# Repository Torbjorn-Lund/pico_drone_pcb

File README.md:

# pico_drone_pcb

Custom PCB for a Raspberry Pi Pico–powered drone.  

This board integrates the core electronics needed to run a quadcopter, with power regulation, sensor connectors, and interfaces for ESCs and other peripherals.

The corresponding code, written in c can be found [here](https://github.com/Torbjorn-Lund/pico_drone_project)

## Features
- Designed for **Raspberry Pi Pico 2**  
- Power regulation:
  - Buck converter supporting up to **18 V input**
  - **TVS diode protection** limiting input voltage to ~10 V  
  - Optimized for **2S LiPo batteries (≈7.4 V nominal, 8.4 V fully charged)**  
- Breakouts for:
  - ESCs (dshot)
  - IMU (ICM-20948)  
  - Barometer (BMP280)  
  - GPS (NEO-M8N)  
  - Time-of-flight sensor (VL53L1X)  

## Images

## Notes / Limitations
- TVS diode limits voltage, so this board is not suitable for 3S+ LiPo packs.  
- Board is still under development.

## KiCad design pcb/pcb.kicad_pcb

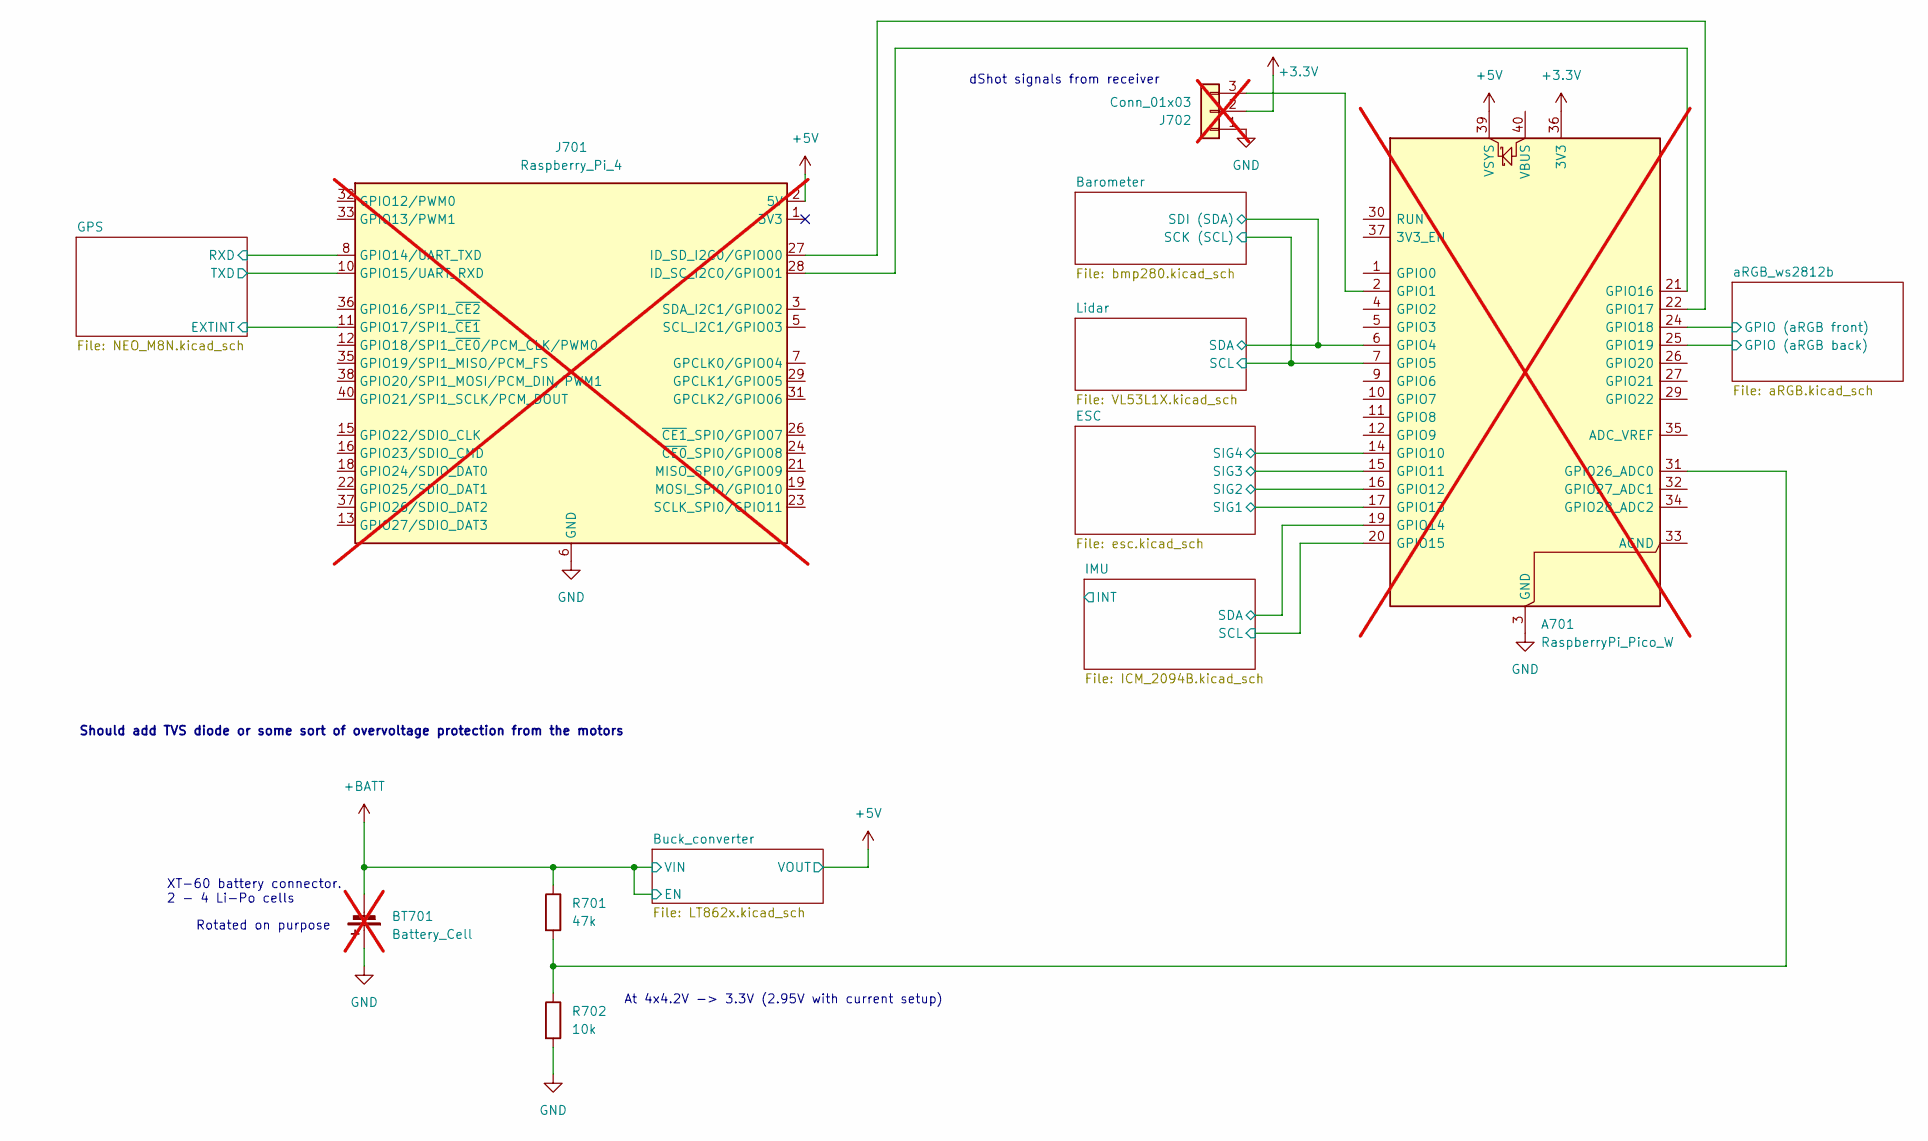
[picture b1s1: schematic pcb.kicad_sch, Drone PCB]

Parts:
A701: RaspberryPi_Pico_W; RaspberryPi_Pico_SMD_HandSolder; DigiKey 0; not fitted
BT701: Battery_Cell; AMASS_XT60-M_1x02_P7.20mm_Vertical; DigiKey 1738-1437-ND; not fitted
J701: Raspberry_Pi_4; PinSocket_2x20_P2.54mm_Vertical; not fitted
J702: Conn_01x03; PinHeader_1x03_P2.54mm_Horizontal; not fitted
R701: 47k; R_0402_1005Metric_Pad0.72x0.64mm_HandSolder
R702: 10k; R_0402_1005Metric_Pad0.72x0.64mm_HandSolder

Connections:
+3.3V: A701.36 (3V3), J702.2; also elsewhere on the board
+5V: A701.39 (VSYS), J701.2 (5V), J701.4 (5V); also elsewhere on the board
+BATT: BT701.2 (-), R701.1; also elsewhere on the board
/Barometer/SCK (SCL): A701.7 (GPIO5); also elsewhere on the board
/Barometer/SDI (SDA): A701.6 (GPIO4); also elsewhere on the board
/ESC/SIG1: A701.17 (GPIO13); also elsewhere on the board
/ESC/SIG2: A701.16 (GPIO12); also elsewhere on the board
/ESC/SIG3: A701.15 (GPIO11); also elsewhere on the board
/ESC/SIG4: A701.14 (GPIO10); also elsewhere on the board
/GPS/EXTINT: J701.11 (GPIO17/SPI1_~CE1); also elsewhere on the board
/GPS/RXD: J701.8 (GPIO14/UART_TXD); also elsewhere on the board
/GPS/TXD: J701.10 (GPIO15/UART_RXD); also elsewhere on the board
/IMU/SCL: A701.20 (GPIO15); also elsewhere on the board
/IMU/SDA: A701.19 (GPIO14); also elsewhere on the board
/aRGB_ws2812b/GPIO (aRGB back): A701.25 (GPIO19); also elsewhere on the board
/aRGB_ws2812b/GPIO (aRGB front): A701.24 (GPIO18); also elsewhere on the board
GND: A701.3 (GND), A701.8 (GND), A701.13 (GND), A701.18 (GND), A701.23 (GND), A701.28 (GND), A701.38 (GND), BT701.1 (+), J701.6 (GND), J701.9 (GND), J701.14 (GND), J701.20 (GND), J701.25 (GND), J701.30 (GND), J701.34 (GND), J701.39 (GND), J702.1, R702.2; also elsewhere on the board
unnamed: A701.2 (GPIO1), J702.3
unnamed: A701.21 (GPIO16), J701.28 (ID_SC_I2C0/GPIO01)
unnamed: A701.22 (GPIO17), J701.27 (ID_SD_I2C0/GPIO00)
unnamed: A701.31 (GPIO26_ADC0), R701.2, R702.1

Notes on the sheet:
At 4x4.2V -> 3.3V (2.95V with current setup)
Rotated on purpose
dShot signals from receiver
XT-60 battery connector. 2 - 4 Li-Po cells
Should add TVS diode or some sort of overvoltage protection from the motors

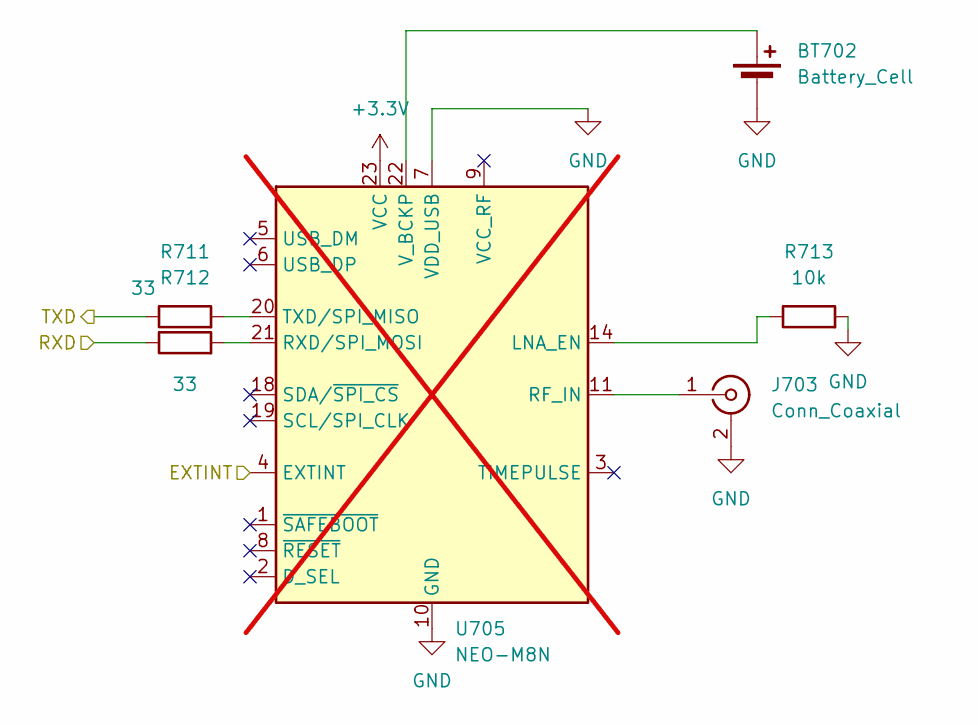
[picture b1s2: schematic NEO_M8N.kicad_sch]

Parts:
BT702: Battery_Cell; BatteryHolder_Keystone_3034_1x20mm; DigiKey 36-3034-ND
J703: Conn_Coaxial; U.FL_Hirose_U.FL-R-SMT-1_Vertical; DigiKey 26-U.FL-R-SMT-1(60)CT-ND
R711, R712: 33; R_0402_1005Metric_Pad0.72x0.64mm_HandSolder
R713: 10k; R_0402_1005Metric_Pad0.72x0.64mm_HandSolder
U705: NEO-M8N; ublox_NEO; DigiKey 672-NEO-M8N-0CT-ND; not fitted

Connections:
+3.3V: U705.23 (VCC); also elsewhere on the board
/GPS/EXTINT: U705.4 (EXTINT); also elsewhere on the board
/GPS/RXD: R712.1; also elsewhere on the board
/GPS/TXD: R711.1; also elsewhere on the board
GND: BT702.2 (-), J703.2 (Ext), R713.2, U705.7 (VDD_USB), U705.10 (GND), U705.12 (GND), U705.13 (GND), U705.24 (GND); also elsewhere on the board
unnamed: BT702.1 (+), U705.22 (V_BCKP)
unnamed: J703.1 (In), U705.11 (RF_IN)
unnamed: R713.1, U705.14 (LNA_EN)
unnamed: R712.2, U705.21 (RXD/SPI_MOSI)
unnamed: R711.2, U705.20 (TXD/SPI_MISO)

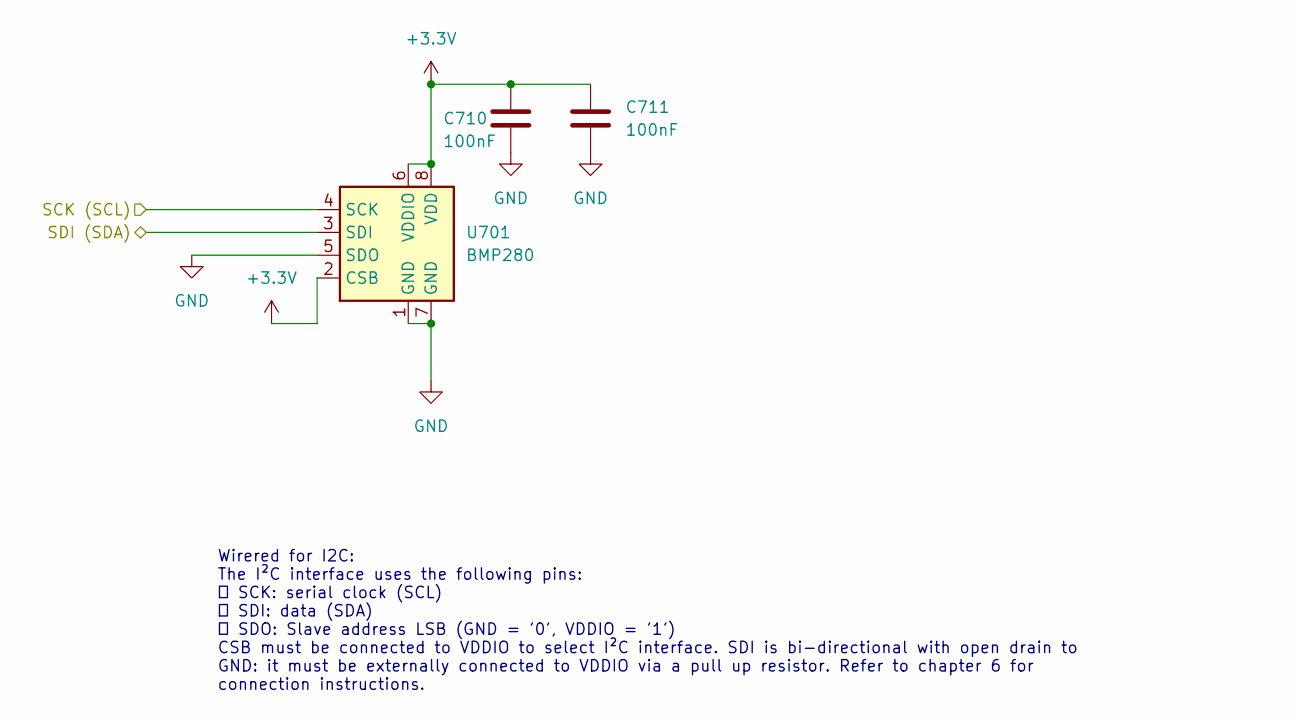
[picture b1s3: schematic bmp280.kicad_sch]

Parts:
C710, C711: 100nF; C_0402_1005Metric_Pad0.74x0.62mm_HandSolder
U701: BMP280; Bosch_LGA-8_2x2.5mm_P0.65mm_ClockwisePinNumbering; DigiKey 828-1064-2-ND

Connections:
+3.3V: C710.1, C711.1, U701.2 (CSB), U701.6 (VDDIO), U701.8 (VDD); also elsewhere on the board
/Barometer/SCK (SCL): U701.4 (SCK); also elsewhere on the board
/Barometer/SDI (SDA): U701.3 (SDI); also elsewhere on the board
GND: C710.2, C711.2, U701.1 (GND), U701.5 (SDO), U701.7 (GND); also elsewhere on the board

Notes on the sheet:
Wirered for I2C: The I²C interface uses the following pins:  SCK: serial clock (SCL)  SDI: data (SDA)  SDO: Slave address LSB (GND = '0', VDDIO = '1') CSB must be connected to VDDIO to select I²C interface. SDI is bi-directional with open drain to GND: it must be externally connected to VDDIO vi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

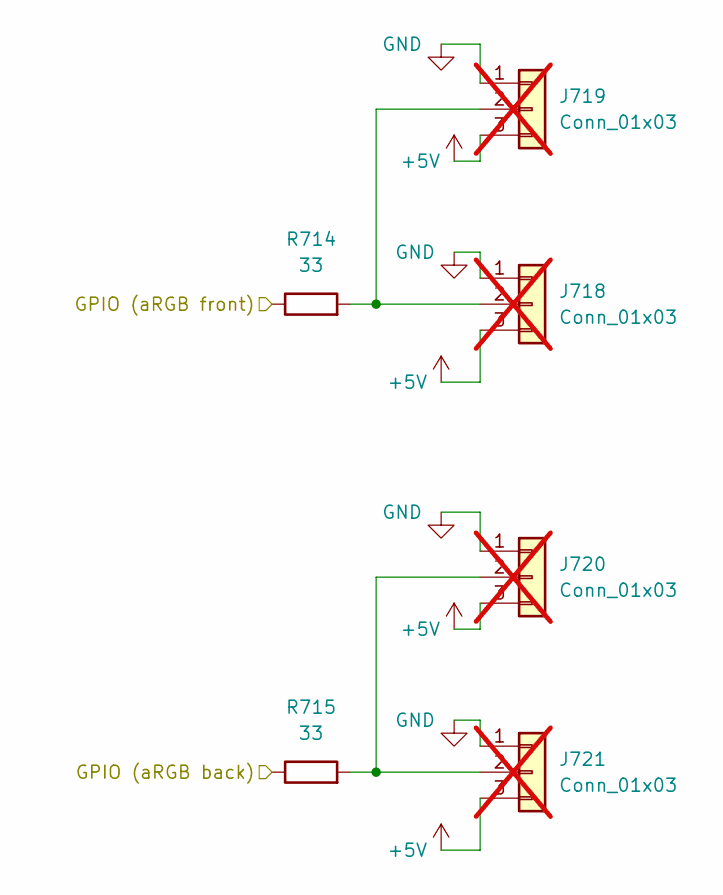
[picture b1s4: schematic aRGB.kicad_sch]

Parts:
J718, J719, J720, J721: Conn_01x03; aRGB_LED_PAD_CONN; not fitted
R714, R715: 33; R_0402_1005Metric_Pad0.72x0.64mm_HandSolder

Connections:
+5V: J718.3, J719.3, J720.3, J721.3; also elsewhere on the board
/aRGB_ws2812b/GPIO (aRGB back): R715.1; also elsewhere on the board
/aRGB_ws2812b/GPIO (aRGB front): R714.1; also elsewhere on the board
GND: J718.1, J719.1, J720.1, J721.1; also elsewhere on the board
unnamed: J718.2, J719.2, R714.2
unnamed: J720.2, J721.2, R715.2

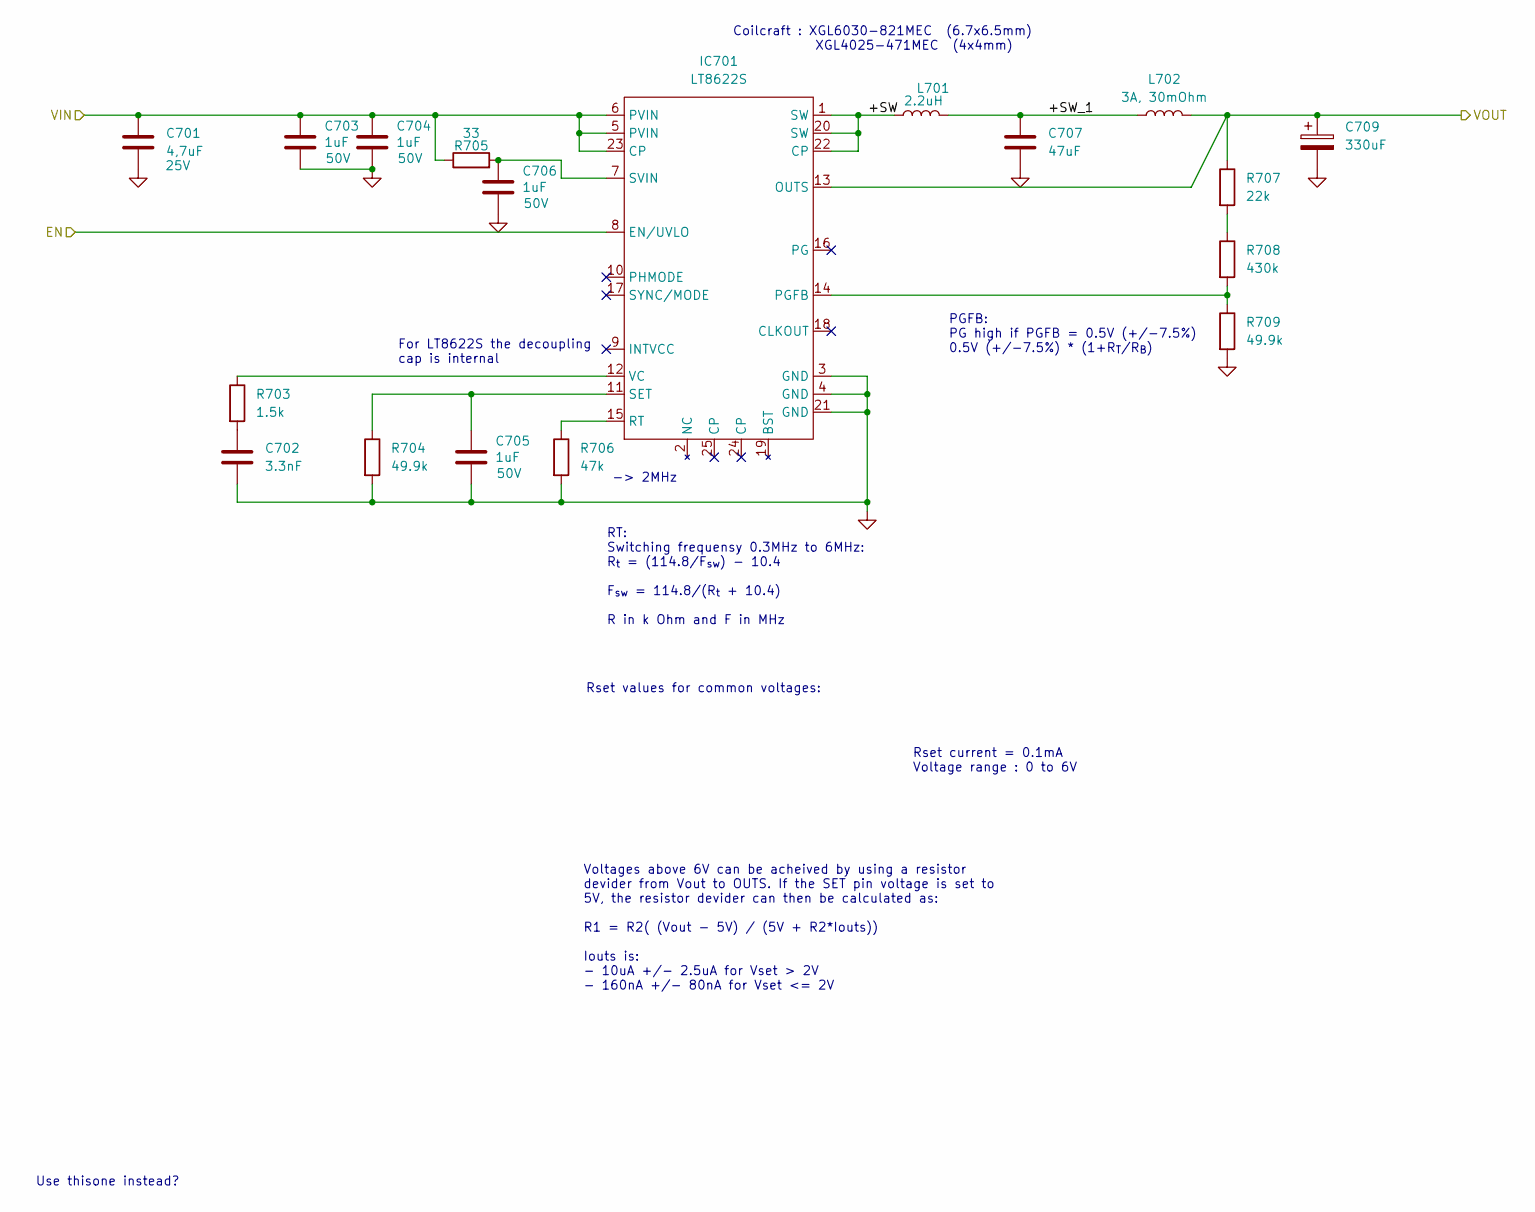
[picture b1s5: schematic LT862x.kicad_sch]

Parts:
C701: 4,7uF; C_0402_1005Metric_Pad0.74x0.62mm_HandSolder; Voltage 25V; DigiKey 490-GRM155C61E475ME15DCT-ND
C702: 3.3nF; C_0402_1005Metric_Pad0.74x0.62mm_HandSolder
C703, C704, C705, C706: 1uF; C_0402_1005Metric_Pad0.74x0.62mm_HandSolder; Voltage 50V; DigiKey 490-GRM155R61H105KE05DCT-ND
C707: 47uF; C_1206_3216Metric_Pad1.33x1.80mm_HandSolder; DigiKey 445-8047-1-ND
C709: 330uF; CAPMP7343X430N
IC701: LT8622S; QFN-20; DigiKey 505-LT8622SAV#PBF-ND
L701: 2.2uH; L_Coilcraft_XAL6060-XXX; DigiKey 4044-CSEG0660-2R2MCT-ND
L702: 3A, 30mOhm; L_0603_1608Metric_Pad1.05x0.95mm_HandSolder; DigiKey 490-5254-1-ND
R703: 1.5k; R_0402_1005Metric_Pad0.72x0.64mm_HandSolder
R704, R709: 49.9k; R_0402_1005Metric_Pad0.72x0.64mm_HandSolder
R705: 33; R_0402_1005Metric_Pad0.72x0.64mm_HandSolder
R706: 47k; R_0402_1005Metric_Pad0.72x0.64mm_HandSolder
R707: 22k; R_0402_1005Metric_Pad0.72x0.64mm_HandSolder
R708: 430k; R_0402_1005Metric_Pad0.72x0.64mm_HandSolder

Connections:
+5V: C709.1, IC701.13 (OUTS), L702.2, R707.1; also elsewhere on the board
+BATT: C701.1, C703.1, C704.1, IC701.5 (PVIN), IC701.6 (PVIN), IC701.8 (EN/UVLO), IC701.23 (CP), R705.1; also elsewhere on the board
/Buck_converter/+SW: IC701.1 (SW), IC701.20 (SW), IC701.22 (CP), L701.1
/Buck_converter/+SW_1: C707.1, L701.2, L702.1
GND: C701.2, C702.2, C703.2, C704.2, C705.2, C706.2, C707.2, C709.2, IC701.3 (GND), IC701.4 (GND), IC701.21 (GND), R704.2, R706.2, R709.2; also elsewhere on the board
unnamed: C702.1, R703.2
unnamed: IC701.14 (PGFB), R708.2, R709.1
unnamed: IC701.15 (RT), R706.1
unnamed: C705.1, IC701.11 (SET), R704.1
unnamed: C706.1, IC701.7 (SVIN), R705.2
unnamed: IC701.12 (VC), R703.1
unnamed: R707.2, R708.1

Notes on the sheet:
-> 2MHz
Rset current = 0.1mA Voltage range : 0 to 6V
PGFB: PG high if PGFB = 0.5V (+/-7.5%) 0.5V (+/-7.5%) * (1+R_{T}/R_{B})
For LT8622S the decoupling cap is internal
Voltages above 6V can be acheived by using a resistor devider from Vout to OUTS. If the SET pin voltage is set to 5V, the resistor devider can then be calculated as: R1 = R2( (Vout - 5V) / (5V + R2*Iouts)) Iouts is: - 10uA +/- 2.5uA for Vset > 2V - 160nA +/- 80nA for Vset <= 2V
Rset values for common voltages:
RT: Switching frequensy 0.3MHz to 6MHz: R_{t} = (114.8/F_{sw}) - 10.4 F_{sw} = 114.8/(R_{t} + 10.4) R in k Ohm and F in MHz
Use thisone instead?
Coilcraft : XGL6030-821MEC (6.7x6.5mm) XGL4025-471MEC (4x4mm)

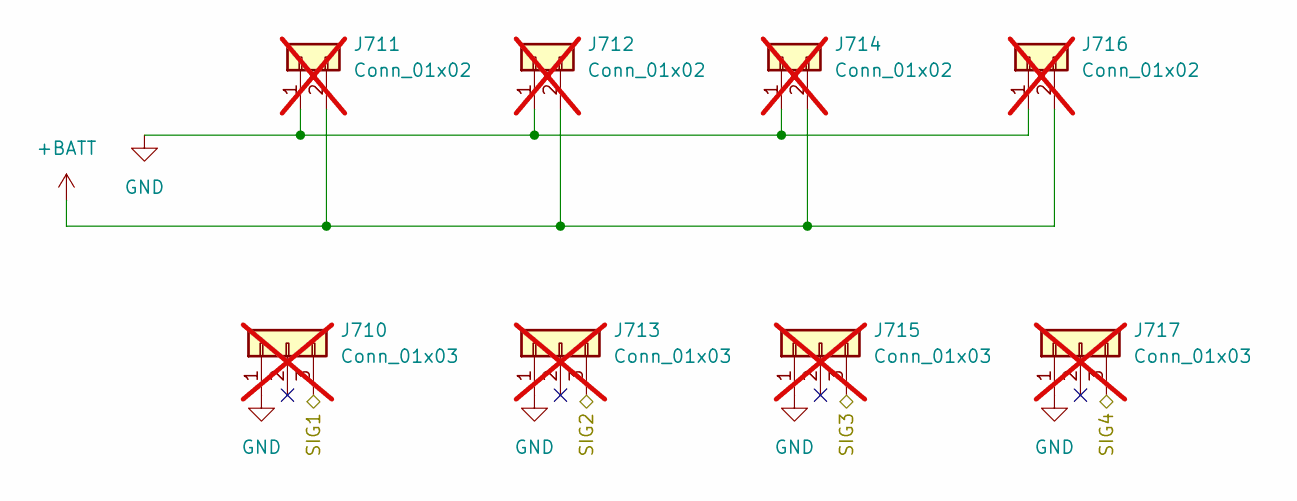
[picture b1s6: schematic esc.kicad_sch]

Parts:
J710, J713, J715, J717: Conn_01x03; PinHeader_1x03_P2.54mm_Horizontal; not fitted
J711, J712, J714, J716: Conn_01x02; ESC_Power_Pad_01x02; not fitted

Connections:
+BATT: J711.2, J712.2, J714.2, J716.2; also elsewhere on the board
/ESC/SIG1: J710.3; also elsewhere on the board
/ESC/SIG2: J713.3; also elsewhere on the board
/ESC/SIG3: J715.3; also elsewhere on the board
/ESC/SIG4: J717.3; also elsewhere on the board
GND: J710.1, J711.1, J712.1, J713.1, J714.1, J715.1, J716.1, J717.1; also elsewhere on the board

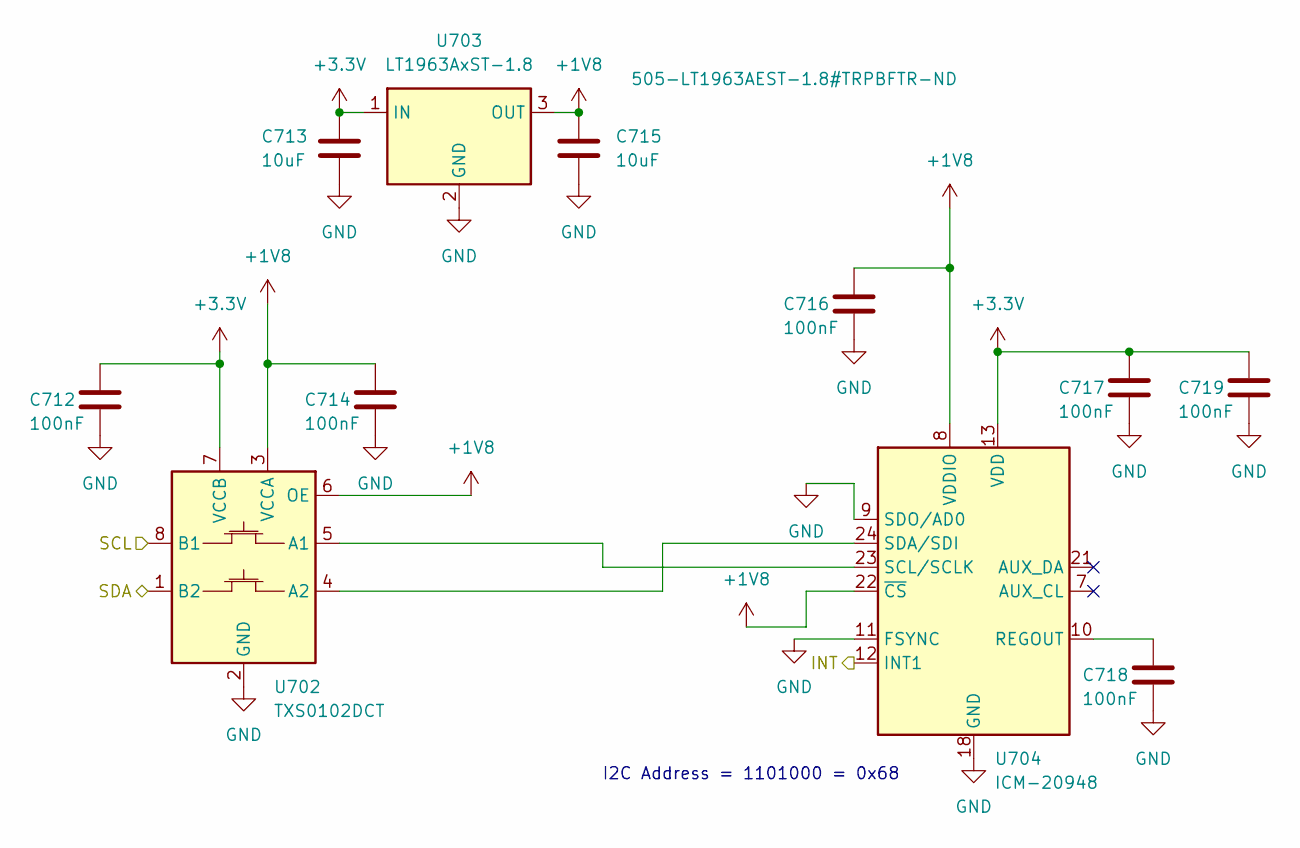
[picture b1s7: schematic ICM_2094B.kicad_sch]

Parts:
C712, C714, C716, C717, C718, C719: 100nF; C_0402_1005Metric_Pad0.74x0.62mm_HandSolder
C713, C715: 10uF; C_0402_1005Metric_Pad0.74x0.62mm_HandSolder
U702: TXS0102DCT; SSOP-8_2.95x2.8mm_P0.65mm; DigiKey 296-TXS0102DCTRCT-ND
U703: LT1963AxST-1.8; SOT-223-3_TabPin2; DigiKey 505-LT1963AEST-1.8#TRPBFTR-ND
U704: ICM-20948; InvenSense_QFN-24_3x3mm_P0.4mm; DigiKey 1428-1123-1-ND

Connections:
+3.3V: C712.1, C713.1, C717.1, C719.1, U702.7 (VCCB), U703.1 (IN), U704.13 (VDD); also elsewhere on the board
/IMU/INT: U704.12 (INT1)
/IMU/SCL: U702.8 (B1); also elsewhere on the board
/IMU/SDA: U702.1 (B2); also elsewhere on the board
GND: C712.2, C713.2, C714.2, C715.2, C716.2, C717.2, C718.2, C719.2, U702.2 (GND), U703.2 (GND), U704.9 (SDO/AD0), U704.11 (FSYNC), U704.18 (GND), U704.20 (GND); also elsewhere on the board
unnamed: U702.5 (A1), U704.23 (SCL/SCLK)
unnamed: U702.4 (A2), U704.24 (SDA/SDI)
unnamed: C718.1, U704.10 (REGOUT)

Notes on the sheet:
I2C Address = 1101000 = 0x68

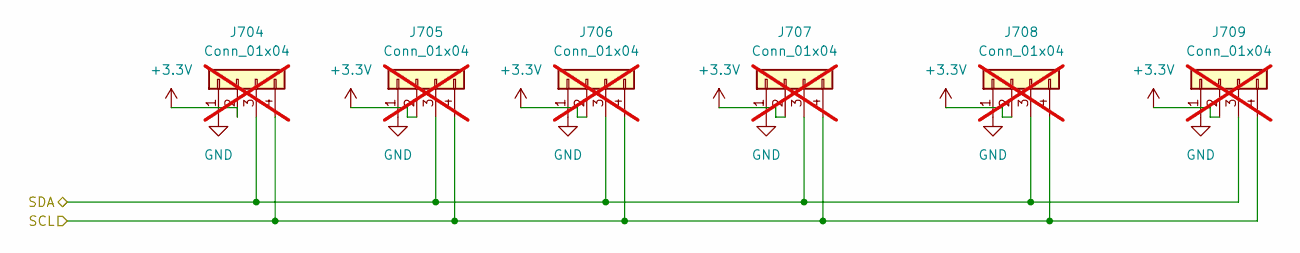
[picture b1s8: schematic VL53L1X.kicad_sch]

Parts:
J704, J705, J706, J707, J708, J709: Conn_01x04; PinHeader_1x04_P2.54mm_Horizontal; not fitted

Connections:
+3.3V: J704.2, J705.2, J706.2, J707.2, J708.2, J709.2; also elsewhere on the board
/Barometer/SCK (SCL): J704.4, J705.4, J706.4, J707.4, J708.4, J709.4; also elsewhere on the board
/Barometer/SDI (SDA): J704.3, J705.3, J706.3, J707.3, J708.3, J709.3; also elsewhere on the board
GND: J704.1, J705.1, J706.1, J707.1, J708.1, J709.1; also elsewhere on the board

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
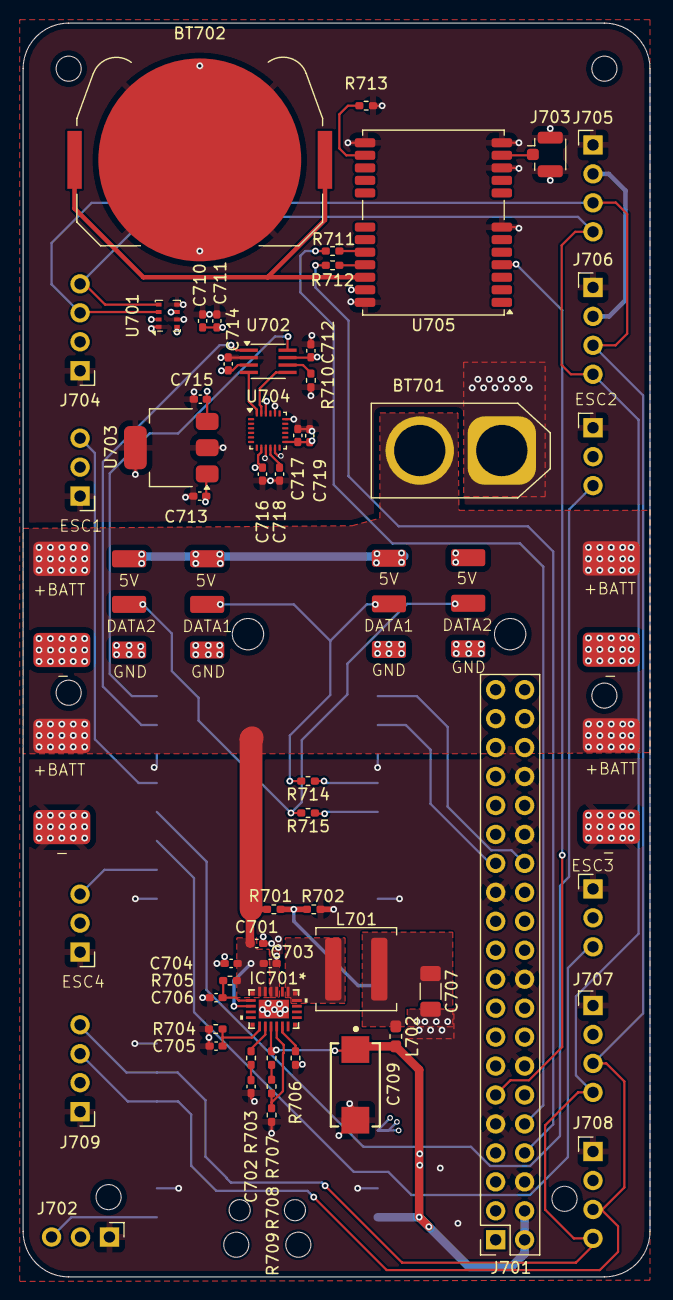
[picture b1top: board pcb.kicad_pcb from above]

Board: 4 copper layers, 55.0 x 110.0 mm, 65 parts (1 on the bottom side), 42 nets.

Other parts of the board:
R710: 10k; R_0402_1005Metric_Pad0.72x0.64mm_HandSolder

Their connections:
GND: R710.2; also elsewhere on the board

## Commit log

2025-08-22 More detailed readme file
2025-08-24 Added images
2025-08-24 Removed png from gitignore

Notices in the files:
README.md:
License: TBD
